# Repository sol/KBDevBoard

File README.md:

# KBDevBoard

KBDevBoard is a development board for rapid prototyping of keyboard circuitry.

I use this to test new MCUs with [QMK](https://qmk.fm/) before designing custom
PCBs.

## How to use this with `DIRECT_PINS`?

- Connect `DIRECT_PINS` to the pin headers in the middle.
- Connect the five pin headers at the top to `GND`.
- Don't use any of the pin headers at the bottom.
- Soldering the diodes is not required, but it isn't harmful either.

## How to use this with `COL2ROW`?

- Connect `MATRIX_ROW_PINS` to the pin headers at the top.
- Connect `MATRIX_COL_PINS` to the pin headers at the bottom.
- Don't use any of the pin headers in the middle.
- Make sure that you soldered the diodes.

## Why are there ten pin headers for only five rows at the top?

There are two pin headers for each row.  This is convenient when you want to
connect all rows to `GND`.  Use a jumper each to shortcut pin headers `1 + 2`,
`2 + 3`, `3 + 4` and `4 + 5`.  Connect `GND` to one of the two remaning pin
headers `1` or `5`.

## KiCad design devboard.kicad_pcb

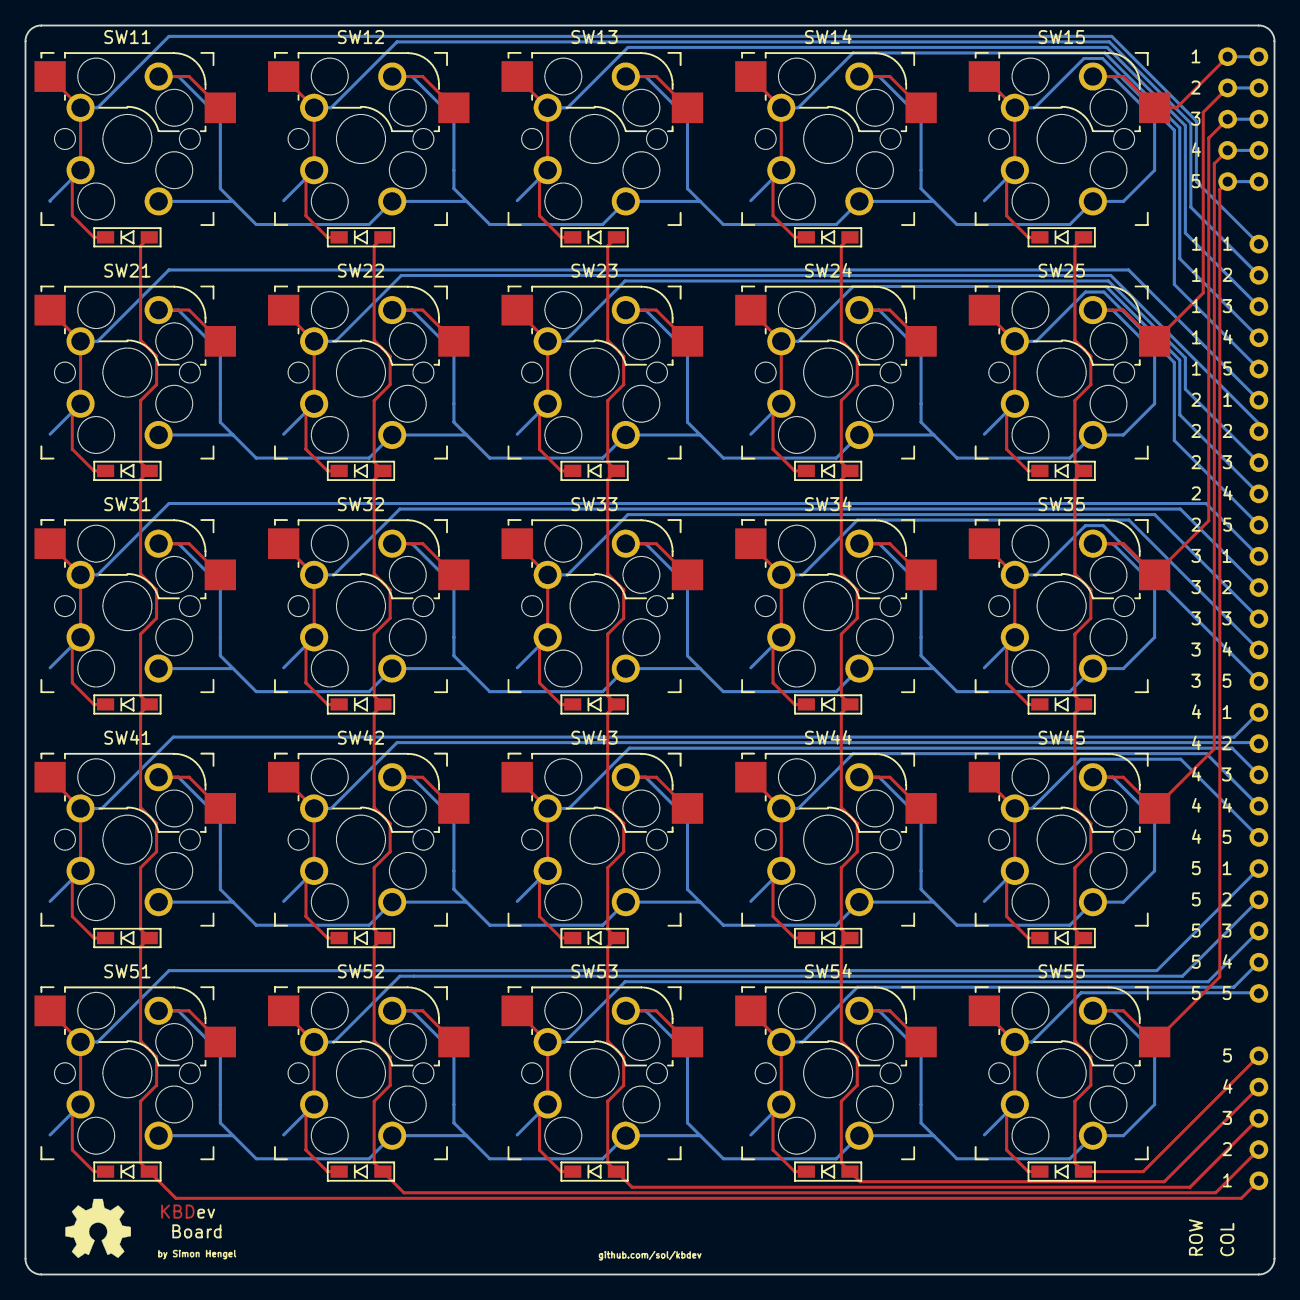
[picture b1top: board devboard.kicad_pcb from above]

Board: 2 copper layers, 101.6 x 101.6 mm, 53 parts (0 on the bottom side), 35 nets.

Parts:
D11, D12, D13, D14, D15, D21, D22, D23, D24, D25, D31, D32, D33, D34, D35, D41, D42, D43, D44, D45, D51, D52, D53, D54, D55: 1N4148; D3_SMD_v2
J1: ROWS
J2: DIRECT
J3: COLUMNS
SW11, SW12, SW13, SW14, SW15, SW21, SW22, SW23, SW24, SW25, SW31, SW32, SW33, SW34, SW35, SW41, SW42, SW43, SW44, SW45, SW51, SW52, SW53, SW54, SW55: SW_PUSH; Kailh_socket_MX_optional_reversible

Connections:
/COL 1: D11.2 (A), D21.2 (A), D31.2 (A), D41.2 (A), D51.2 (A), J3.1
/COL 2: D12.2 (A), D22.2 (A), D32.2 (A), D42.2 (A), D52.2 (A), J3.2
/COL 3: D13.2 (A), D23.2 (A), D33.2 (A), D43.2 (A), D53.2 (A), J3.3
/COL 4: D14.2 (A), D24.2 (A), D34.2 (A), D44.2 (A), D54.2 (A), J3.4
/COL 5: D15.2 (A), D25.2 (A), D35.2 (A), D45.2 (A), D55.2 (A), J3.5
/IN_SW_11: D11.1 (K), J2.1, SW11.1
/IN_SW_12: D12.1 (K), J2.2, SW12.1
/IN_SW_13: D13.1 (K), J2.3, SW13.1
/IN_SW_14: D14.1 (K), J2.4, SW14.1
/IN_SW_15: D15.1 (K), J2.5, SW15.1
/IN_SW_21: D21.1 (K), J2.6, SW21.1
/IN_SW_22: D22.1 (K), J2.7, SW22.1
/IN_SW_23: D23.1 (K), J2.8, SW23.1
/IN_SW_24: D24.1 (K), J2.9, SW24.1
/IN_SW_25: D25.1 (K), J2.10, SW25.1
/IN_SW_31: D31.1 (K), J2.11, SW31.1
/IN_SW_32: D32.1 (K), J2.12, SW32.1
/IN_SW_33: D33.1 (K), J2.13, SW33.1
/IN_SW_34: D34.1 (K), J2.14, SW34.1
/IN_SW_35: D35.1 (K), J2.15, SW35.1
/IN_SW_41: D41.1 (K), J2.16, SW41.1
/IN_SW_42: D42.1 (K), J2.17, SW42.1
/IN_SW_43: D43.1 (K), J2.18, SW43.1
/IN_SW_44: D44.1 (K), J2.19, SW44.1
/IN_SW_45: D45.1 (K), J2.20, SW45.1
/IN_SW_51: D51.1 (K), J2.21, SW51.1
/IN_SW_52: D52.1 (K), J2.22, SW52.1
/IN_SW_53: D53.1 (K), J2.23, SW53.1
/IN_SW_54: D54.1 (K), J2.24, SW54.1
/IN_SW_55: D55.1 (K), J2.25, SW55.1
/ROW 1: J1.1, SW11.2, SW12.2, SW13.2, SW14.2, SW15.2
/ROW 2: J1.2, SW21.2, SW22.2, SW23.2, SW24.2, SW25.2
/ROW 3: J1.3, SW31.2, SW32.2, SW33.2, SW34.2, SW35.2
/ROW 4: J1.4, SW41.2, SW42.2, SW43.2, SW44.2, SW45.2
/ROW 5: J1.5, SW51.2, SW52.2, SW53.2, SW54.2, SW55.2
